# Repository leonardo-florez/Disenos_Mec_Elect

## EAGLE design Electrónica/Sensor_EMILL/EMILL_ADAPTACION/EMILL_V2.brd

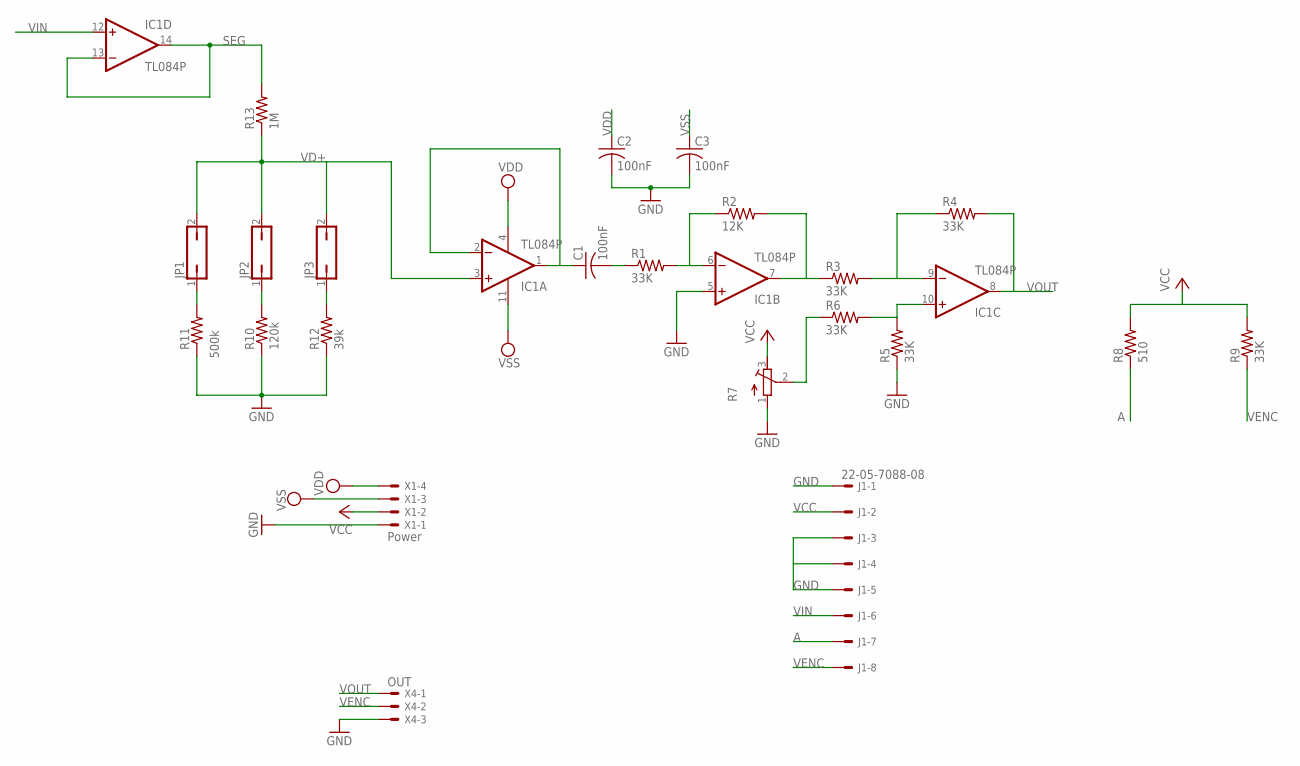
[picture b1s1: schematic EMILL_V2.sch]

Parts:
C1, C2, C3: 100nF; C025-025X050
IC1: TL084P; DIL14
J1: 22-05-7088-08; 7395-08
JP1, JP2, JP3: JP1Q; JP1
R1, R3, R4, R5, R6, R9: 33K; 0207/10
R2: 12K; 0207/10
R7: R-TRIMM64W; RTRIM64W
R8: 510; 0207/10
R10: 120k; 0207/10
R11: 500k; 0207/10
R12: 39k; 0207/10
R13: 1M; 0207/10
X1: Power; 22-23-2041
X4: OUT; 22-23-2031

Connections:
A: J1.7, R8.1
GND: C2.2, C3.2, IC1.5 (+IN), J1.1, J1.3, J1.4, J1.5, R5.1, R7.1 (A), R10.1, R11.1, R12.1, X1.1, X4.3
unnamed: C1.1, IC1.1 (OUT), IC1.2 (-IN)
unnamed: C1.2, R1.1
unnamed: IC1.6 (-IN), R1.2, R2.1
unnamed: IC1.7 (OUT), R2.2, R3.1
unnamed: IC1.9 (-IN), R3.2, R4.1
unnamed: IC1.10 (+IN), R5.2, R6.2
unnamed: R6.1, R7.2 (S)
unnamed: JP2.1, R10.2
unnamed: JP3.1, R12.2
unnamed: JP1.1, R11.2
SEG: IC1.13 (-IN), IC1.14 (OUT), R13.2
VCC: J1.2, R7.3 (E), R8.2, R9.2, X1.2
VD+: IC1.3 (+IN), JP1.2, JP2.2, JP3.2, R13.1
VDD: C2.1, IC1.4 (V+), X1.4
VENC: J1.8, R9.1, X4.2
VIN: IC1.12 (+IN), J1.6
VOUT: IC1.8 (OUT), R4.2, X4.1
VSS: C3.1, IC1.11 (V-), X1.3

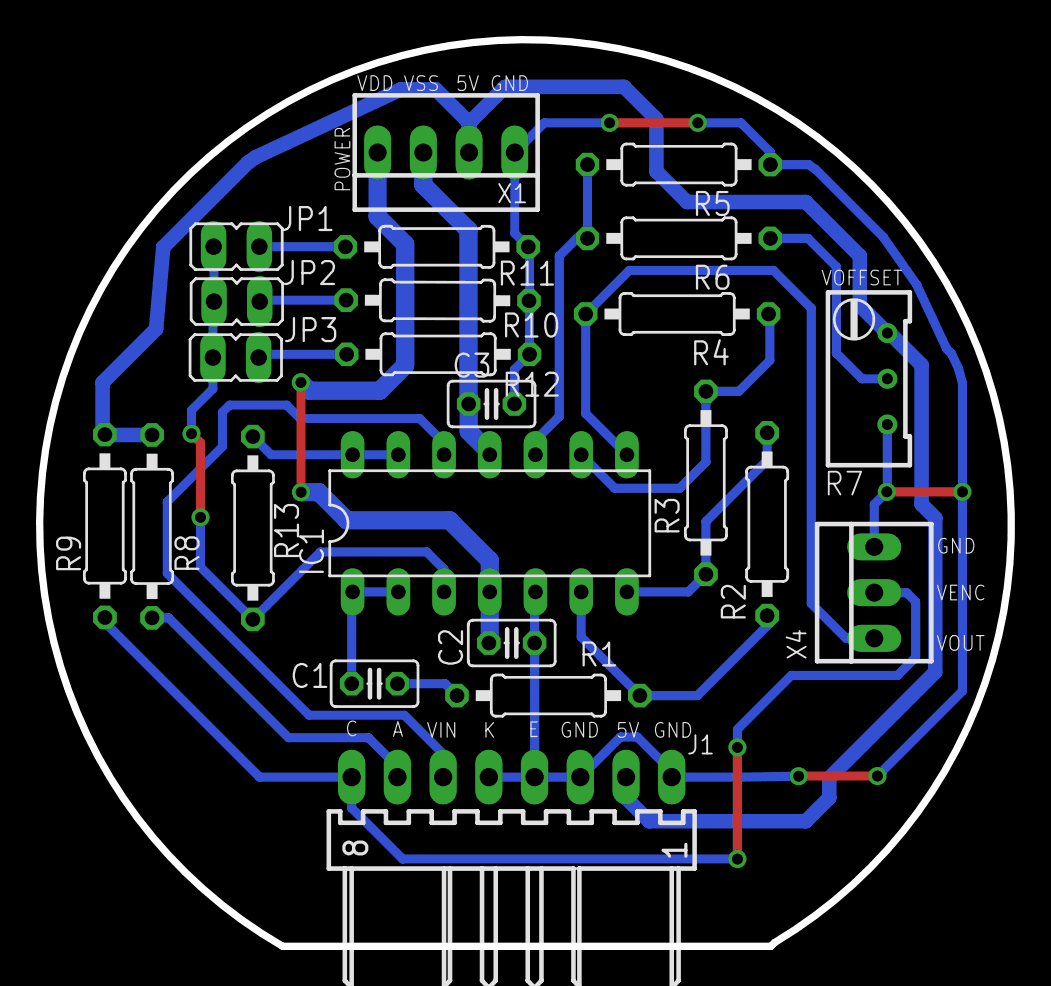
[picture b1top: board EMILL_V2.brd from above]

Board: 2 copper layers, 54.0 x 50.4 mm, 23 parts (0 on the bottom side), 20 nets.

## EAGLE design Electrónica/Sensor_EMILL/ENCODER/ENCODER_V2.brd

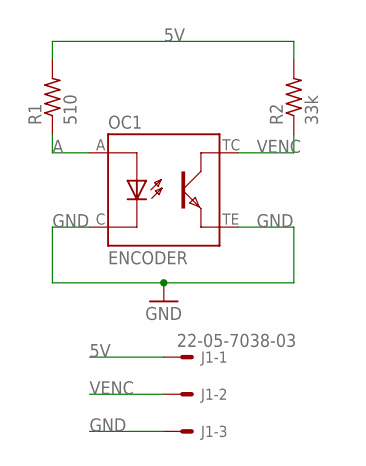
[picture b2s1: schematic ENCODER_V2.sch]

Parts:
J1: 22-05-7038-03; 7395-03
OC1: ENCODER; PI_GP1S53VJ000F
R1: 510; R0805
R2: 33k; R0805

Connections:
5V: J1.1, R1.2, R2.2
A: OC1.A, R1.1
GND: J1.3, OC1.C, OC1.TE
VENC: J1.2, OC1.TC, R2.1

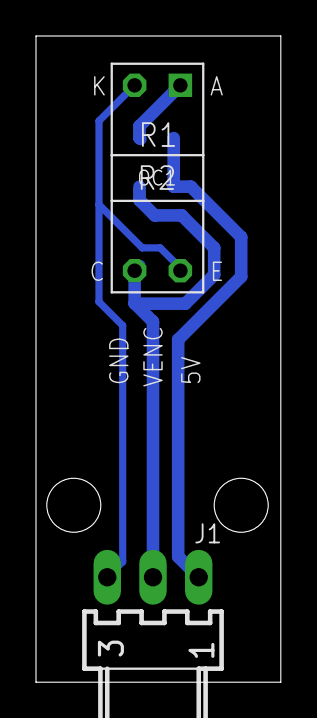
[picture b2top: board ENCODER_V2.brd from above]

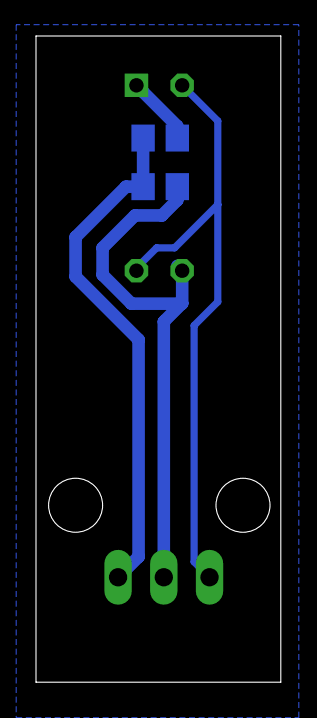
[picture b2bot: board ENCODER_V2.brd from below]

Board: 2 copper layers, 13.6 x 35.9 mm, 4 parts (2 on the bottom side), 4 nets.

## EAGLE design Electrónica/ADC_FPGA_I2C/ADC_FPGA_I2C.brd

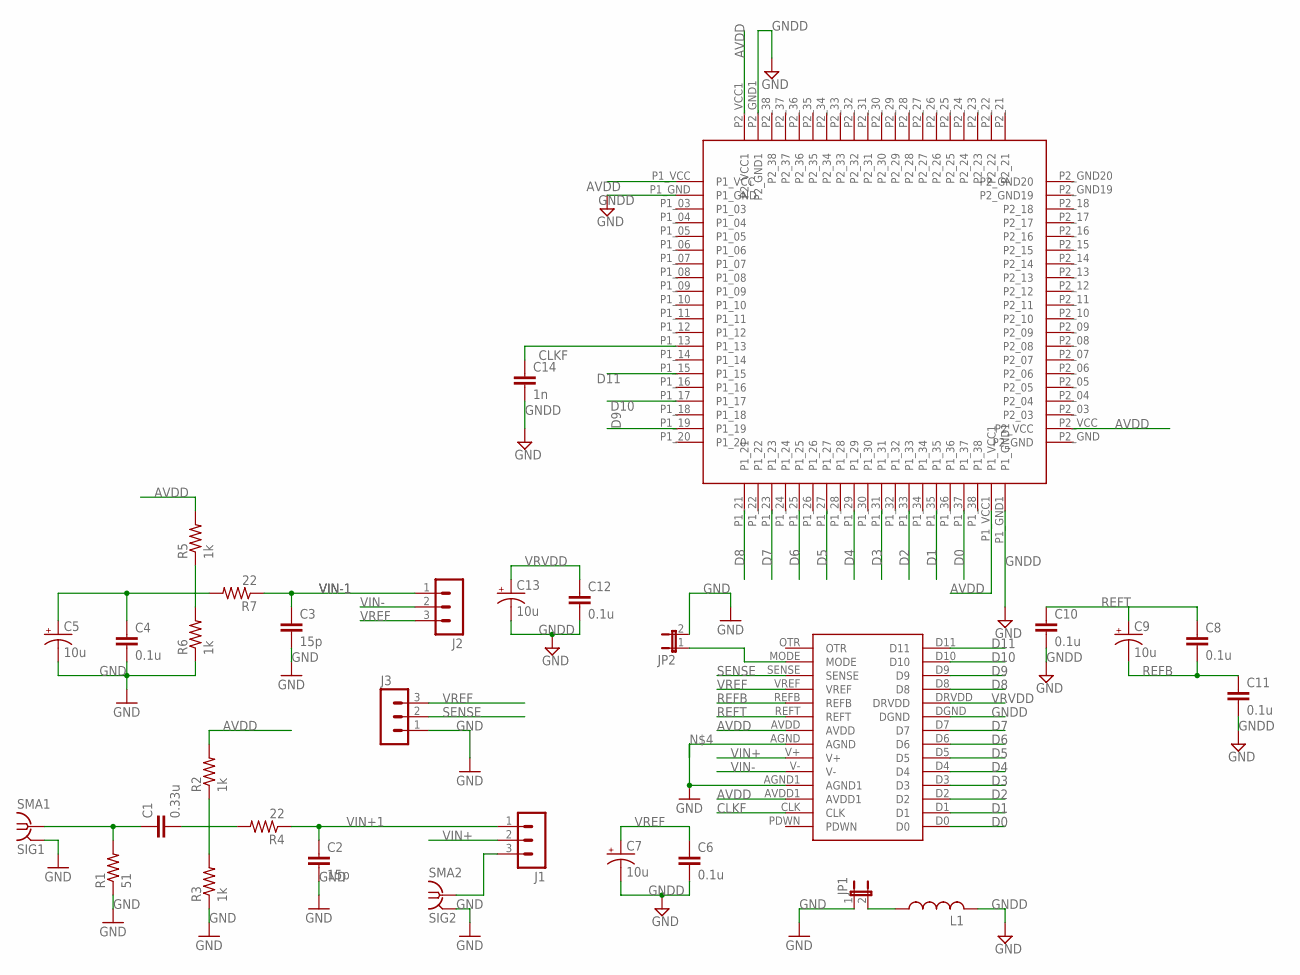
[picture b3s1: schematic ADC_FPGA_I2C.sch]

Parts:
C1: 0.33u; C075-063X106
C2, C3: 15p; C050-024X044
C4, C6, C8, C10, C11, C12: 0.1u; C050-024X044
C5, C7, C9, C13: 10u; E2,5-5
C14: 1n; C050-024X044
J1, J2, J3: MA03-1
JP1, JP2: JP1E; JP1
L1: L-US0204/7; 0204/7
R1: 51; 0207/10
R2, R3, R5, R6: 1k; 0207/10
R4, R7: 22; 0207/10
SMA1: SIG1; SMA-142-0701-871
SMA2: SIG2; SMA-142-0701-871
U$1: AD9235
U$2: SPARTAN_6_NIMAS

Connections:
AVDD: R2.2, R5.2, U$1.AVDD, U$1.AVDD1, U$2.P1_VCC, U$2.P1_VCC1, U$2.P2_VCC, U$2.P2_VCC1
CLKF: C14.1, U$1.CLK, U$2.P1_13
D0: U$1.D0, U$2.P1_37
D1: U$1.D1, U$2.P1_35
D2: U$1.D2, U$2.P1_33
D3: U$1.D3, U$2.P1_31
D4: U$1.D4, U$2.P1_29
D5: U$1.D5, U$2.P1_27
D6: U$1.D6, U$2.P1_25
D7: U$1.D7, U$2.P1_23
D8: U$1.D8, U$2.P1_21
D9: U$1.D9, U$2.P1_19
D10: U$1.D10, U$2.P1_17
D11: U$1.D11, U$2.P1_15
GND: C2.2, C3.2, C4.2, C5.-, J3.1, JP1.1, JP2.2, R1.1, R3.1, R6.1, SMA1.2@1 (2), SMA1.2@2 (2), SMA1.2@3 (2), SMA1.2@4 (2), SMA2.2@1 (2), SMA2.2@2 (2), SMA2.2@3 (2), SMA2.2@4 (2)
GNDD: C6.2, C7.-, C10.2, C11.2, C12.2, C13.-, C14.2, L1.2, U$1.DGND, U$2.P1_GND, U$2.P1_GND1, U$2.P2_GND1
unnamed: C1.1, R1.2, SMA1.1
unnamed: C1.2, R4.2
unnamed: R2.1, R3.2
unnamed: U$1.AGND, U$1.AGND1
unnamed: J1.3, SMA2.1
unnamed: C4.1, C5.+, R7.2
unnamed: R5.1, R6.2
unnamed: JP1.2, L1.1
unnamed: JP2.1, U$1.MODE
REFB: C8.2, C9.-, C11.1, U$1.REFB
REFT: C8.1, C9.+, C10.1, U$1.REFT
SENSE: J3.2, U$1.SENSE
VIN+: J1.2, U$1.V+
VIN+1: C2.1, J1.1, R4.1
VIN-: J2.2, U$1.V-
VIN-1: C3.1, J2.1, R7.1
VREF: C6.1, C7.+, J2.3, J3.3, U$1.VREF
VRVDD: C12.1, C13.+, U$1.DRVDD

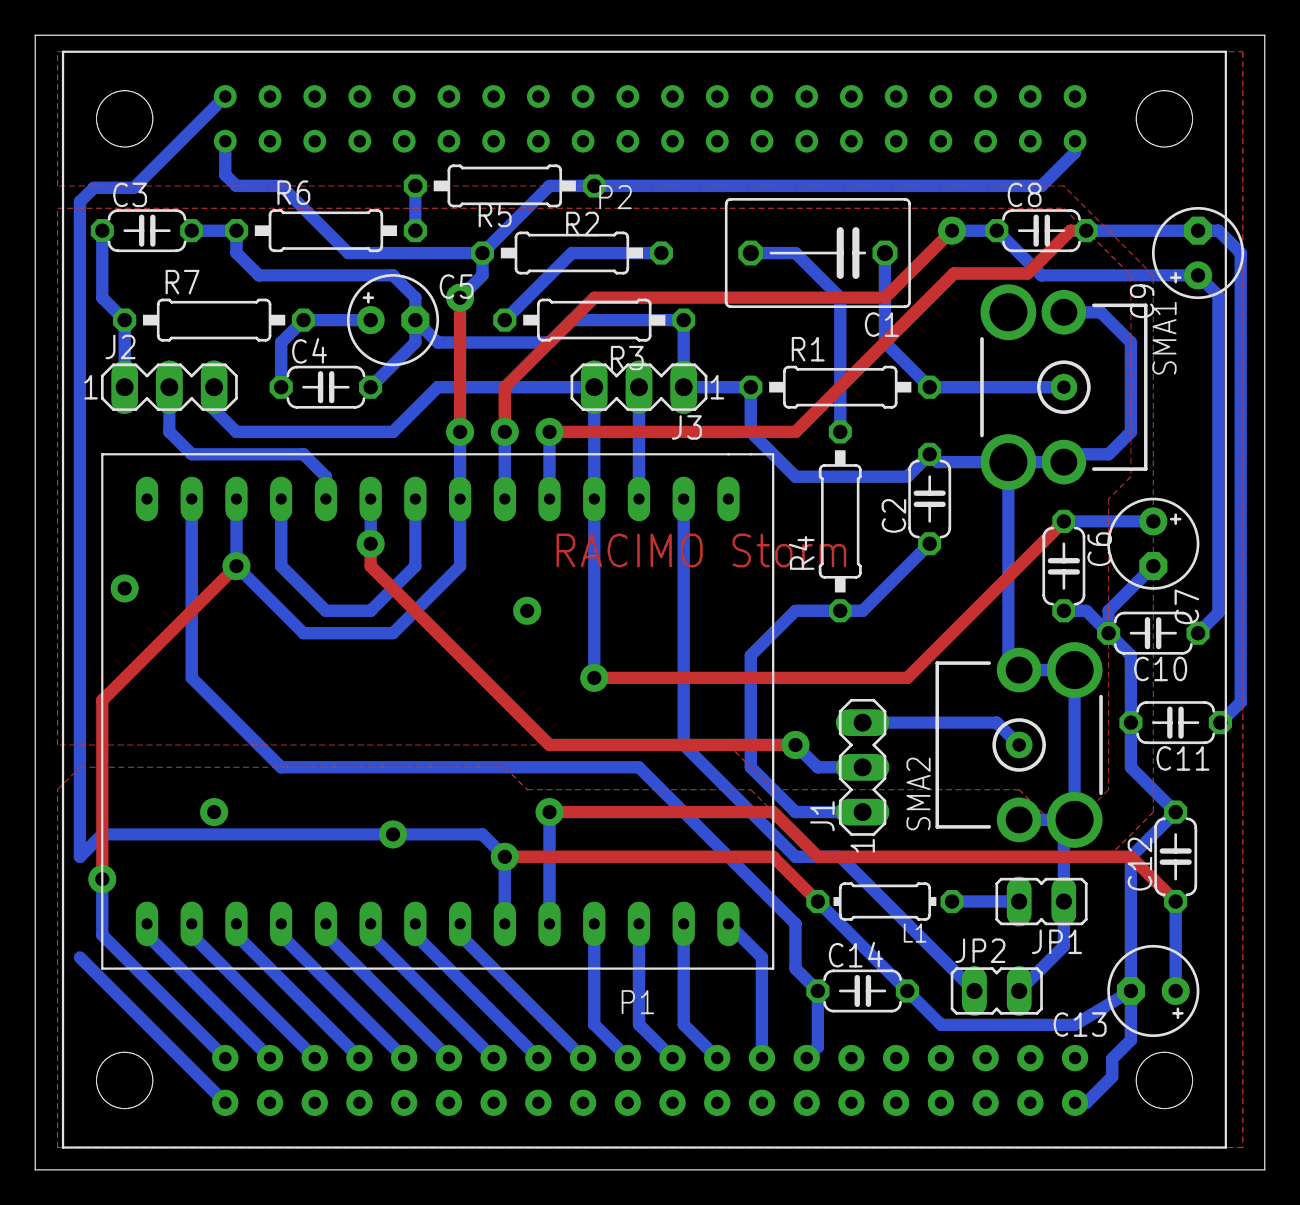
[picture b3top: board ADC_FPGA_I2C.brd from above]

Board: 2 copper layers, 69.8 x 64.4 mm, 31 parts (0 on the bottom side), 34 nets.

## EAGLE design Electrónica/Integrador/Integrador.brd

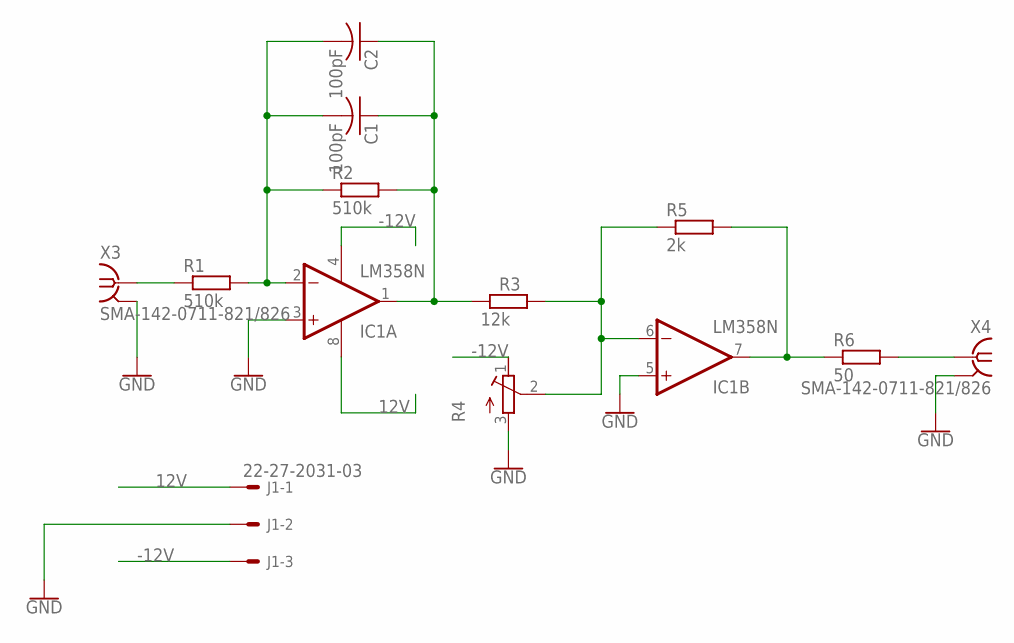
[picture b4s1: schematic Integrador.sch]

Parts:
C1, C2: 100pF; C025-030X050
IC1: LM358N; DIL08
J1: 22-27-2031-03; 6410-03
R1, R2: 510k; 0207/10
R3: 12k; 0207/10
R4: R-TRIMM3006P; RTRIM3006P
R5: 2k; 0207/10
R6: 50; 0207/10
X3, X4: SMA-142-0711-821/826; J502-ND-142-0711-821/826

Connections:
12V: IC1.8 (V+), J1.1
-12V: IC1.4 (V-), J1.3, R4.1 (E)
GND: IC1.3 (+IN), IC1.5 (+IN), J1.2, R4.3 (A), X3.G@1 (2), X3.G@2 (2), X3.G@3 (2), X3.G@4 (2), X4.G@1 (2), X4.G@2 (2), X4.G@3 (2), X4.G@4 (2)
unnamed: R1.1, X3.1
unnamed: C1.2, C2.2, IC1.2 (-IN), R1.2, R2.1
unnamed: C1.1, C2.1, IC1.1 (OUT), R2.2, R3.1
unnamed: IC1.6 (-IN), R3.2, R4.2 (S), R5.1
unnamed: IC1.7 (OUT), R5.2, R6.1
unnamed: R6.2, X4.1

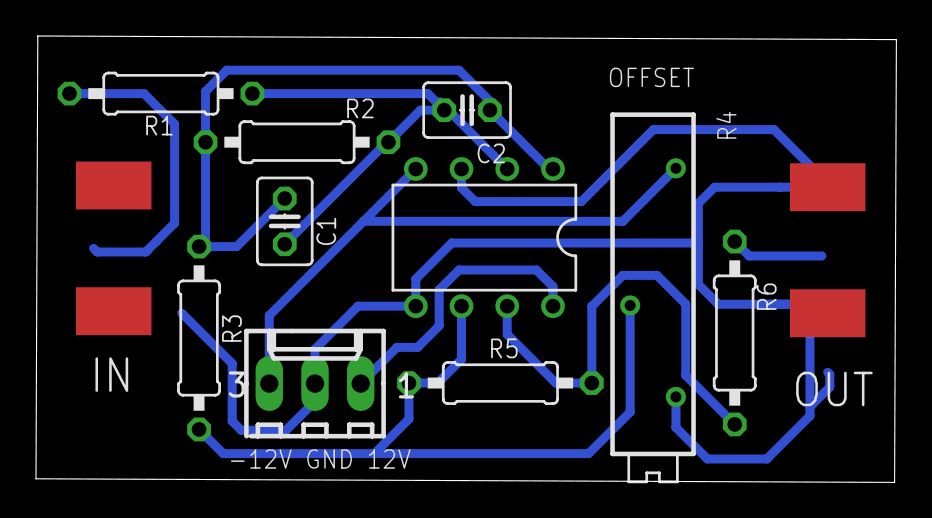
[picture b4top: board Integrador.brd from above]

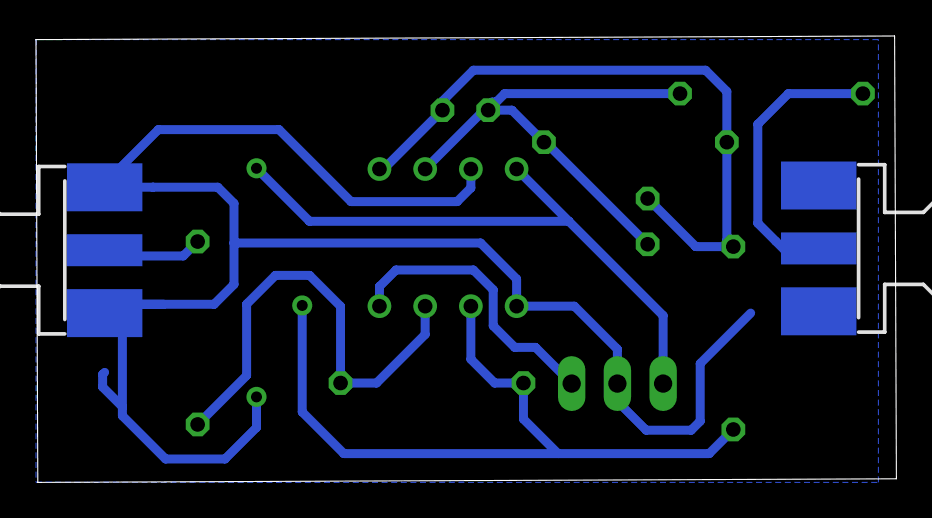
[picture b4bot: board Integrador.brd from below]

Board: 2 copper layers, 47.8 x 24.8 mm, 12 parts (2 on the bottom side), 9 nets.

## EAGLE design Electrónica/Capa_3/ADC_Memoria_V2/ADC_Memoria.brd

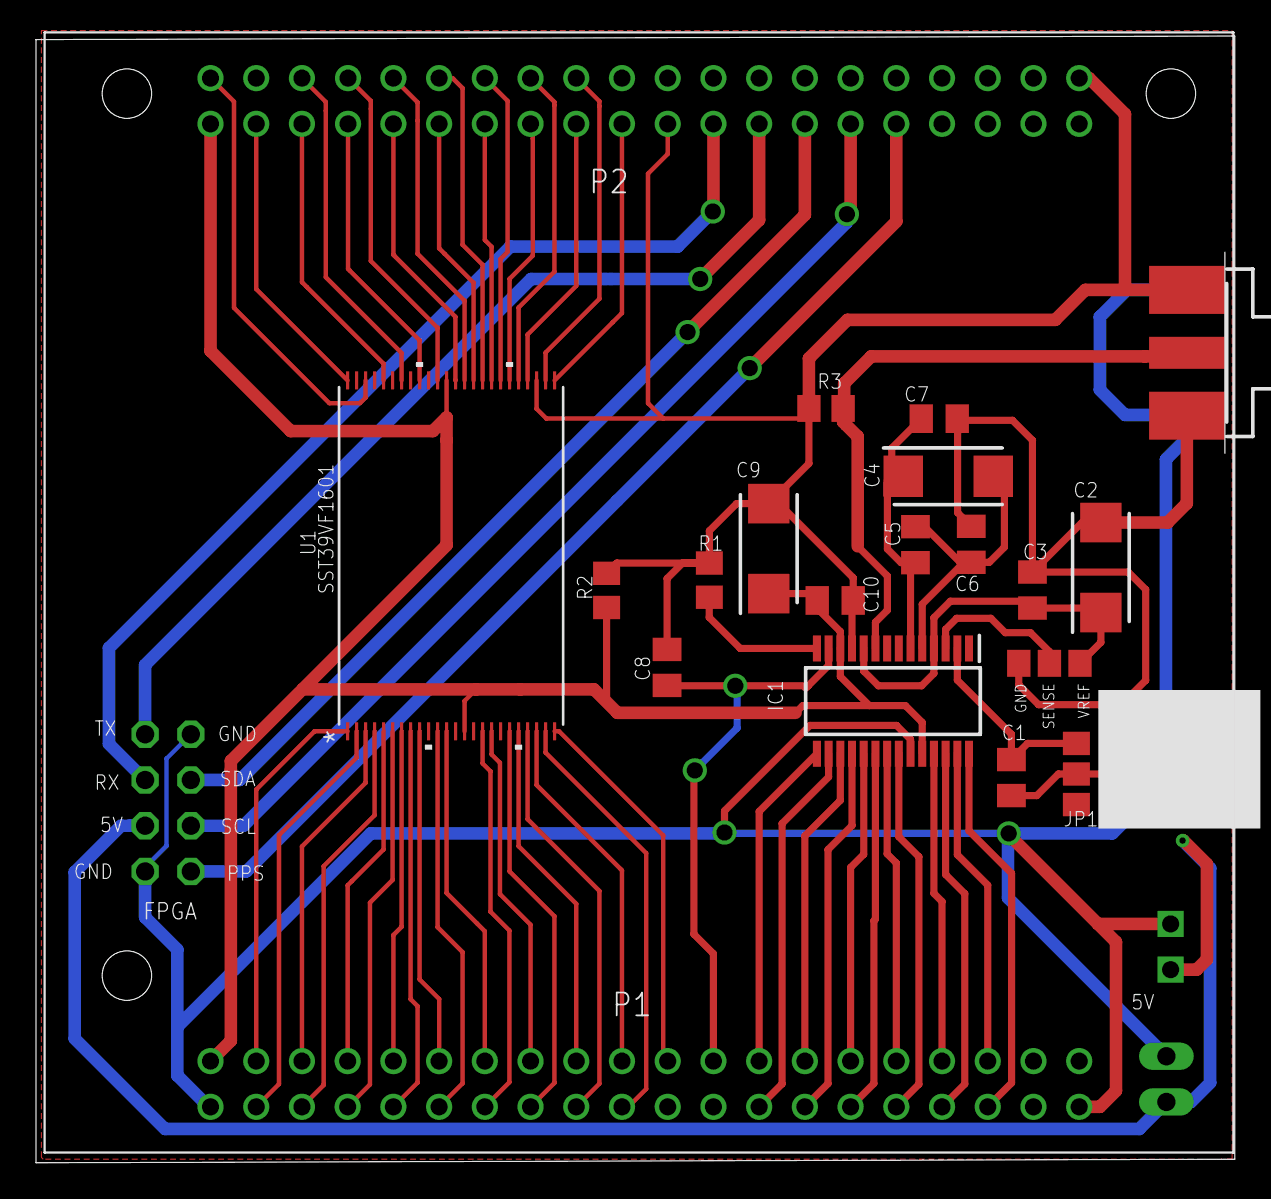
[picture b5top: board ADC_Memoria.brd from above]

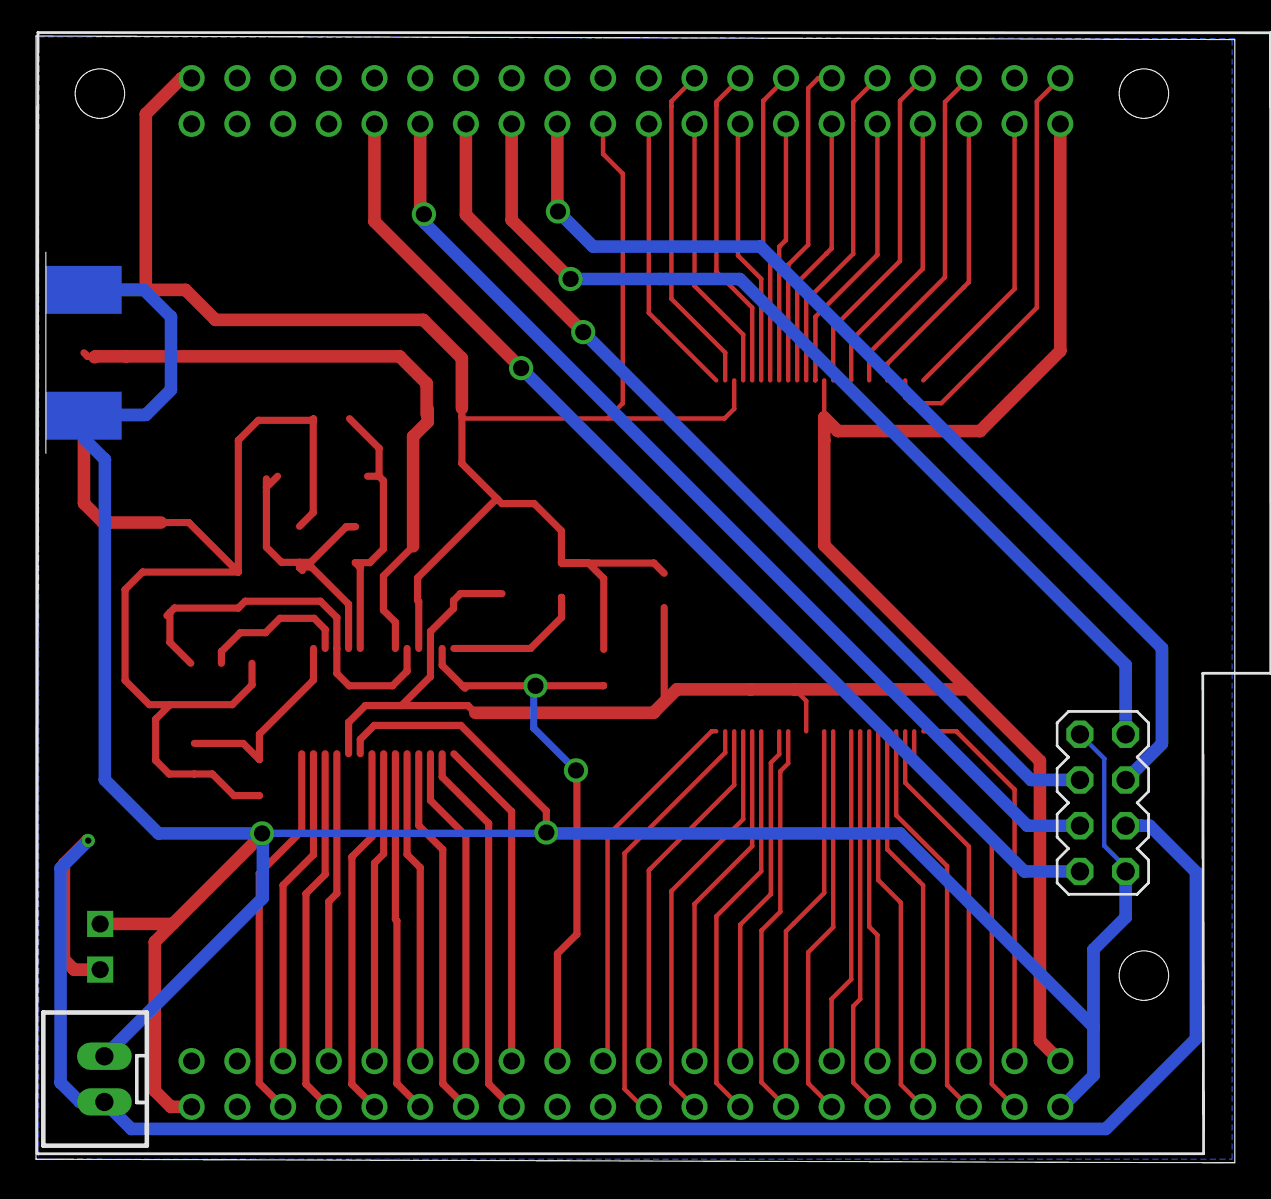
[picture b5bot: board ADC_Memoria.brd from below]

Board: 2 copper layers, 66.6 x 62.6 mm, 21 parts (2 on the bottom side), 63 nets.

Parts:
C1, C3, C5, C6, C7, C10: 0.1uF; C0805K
C2, C4, C9: 10uF; CAPPM6032X280N
C8: 15pF; C0805K
GND-SEN-VREF: JP2; A0R-JMP
IC1: AD9235; SOP65P638X110-28N
JP1: GND MODE; A0R-JMP
R1: 5k; R0805
R2: 10k; R0805
R3: 50; R0805
SMA: SIGNAL; J502-ND-142-0711-821/826
U1: SST39VF1601; TSOP48_EKE_SST-L
U$1: SPARTAN_NO_HOLES
U$2: CAPA1
V_EXT: V_Ext; JST-XH-02-PACKAGE-LONG-PAD

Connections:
5V: U$1.5V_E, U$2.5V, V_EXT.1
A0: U1.25, U$1.P2_22
A1: U1.24, U$1.P1_19
A2: U1.23, U$1.P1_22
A3: U1.22, U$1.P1_21
A4: U1.21, U$1.P1_24
A5: U1.20, U$1.P1_23
A6: U1.19, U$1.P1_26
A8: U1.8, U$1.P1_32
A9: U1.7, U$1.P1_31
A10: U1.6, U$1.P1_34
A11: U1.5, U$1.P1_33
A12: U1.4, U$1.P1_36
A13: U1.3, U$1.P1_35
A14: U1.2, U$1.P1_38
A15: U1.1, U$1.P1_37
A16: U1.48, U$1.P2_38
A17: U1.17, U$1.P1_25
A18: U1.16, U$1.P1_28
A19: U1.9, U$1.P1_29
AVDD: C9.1, C10.1, IC1.12, IC1.24, R2.1, U1.14, U1.37, U$1.P1_VCC1, U$1.P2_VCC1
CE: U1.26, U$1.P2_23
CLK: C8.1, IC1.13, U$1.P1_17
D0: IC1.15, U$1.P1_15
D1: IC1.16, U$1.P1_16
D2: IC1.17, U$1.P1_13
D3: IC1.18, U$1.P1_14
D4: IC1.19, U$1.P1_11
D5: IC1.20, U$1.P1_12
D6: IC1.21, U$1.P1_09
D7: IC1.22, U$1.P1_10
D8: IC1.25, U$1.P1_07
D9: IC1.26, U$1.P1_08
D10: IC1.27, U$1.P1_05
D11: IC1.28, U$1.P1_06
DQ0: U1.29, U$1.P2_25
DQ1: U1.31, U$1.P2_27
DQ2: U1.33, U$1.P2_29
DQ3: U1.35, U$1.P2_31
DQ4: U1.38, U$1.P2_33
DQ5: U1.40, U$1.P2_34
DQ6: U1.42, U$1.P2_35
DQ7: U1.44, U$1.P2_36
DQ8: U1.30, U$1.P2_26
DQ9: U1.32, U$1.P2_28
DQ10: U1.34, U$1.P2_30
DQ11: U1.36, U$1.P2_32
GND: C1.2, C2.2, C3.2, C6.2, C7.2, C8.2, C9.2, C10.2, GND-SEN-VREF.1, IC1.11, IC1.23, JP1.2, R1.1, R2.2, R3.1, SMA.G@1, SMA.G@2, SMA.G@3, SMA.G@4, U1.27, U1.46, U$1.GND_E, U$1.P1_GND, U$1.P1_GND1, U$1.P2_GND, U$1.P2_GND1, U$1.P2_GND20, U$2.GND, U$2.GND2, V_EXT.2
MODE: C1.1, IC1.2, JP1.1
unnamed: IC1.14, R1.2
OE: U1.28, U$1.P2_24
PPS: U$1.P2_10, U$2.PPS
REFB: C4.2, C5.2, C6.1, IC1.5
REFT: C4.1, C5.1, C7.1, IC1.6
RST: U1.12, U$1.P1_27
RX: U$1.P2_18, U$2.RX2PI
SCL: U$1.P2_12, U$2.SCL
SDA: U$1.P2_14, U$2.SDA
SENSE: GND-SEN-VREF.2, IC1.3
TX: U$1.P2_16, U$2.TX2PI
VIN: IC1.9, R3.2, SMA.1
VREF: C2.1, C3.1, GND-SEN-VREF.3, IC1.4, IC1.10
WE: U1.11, U$1.P1_30

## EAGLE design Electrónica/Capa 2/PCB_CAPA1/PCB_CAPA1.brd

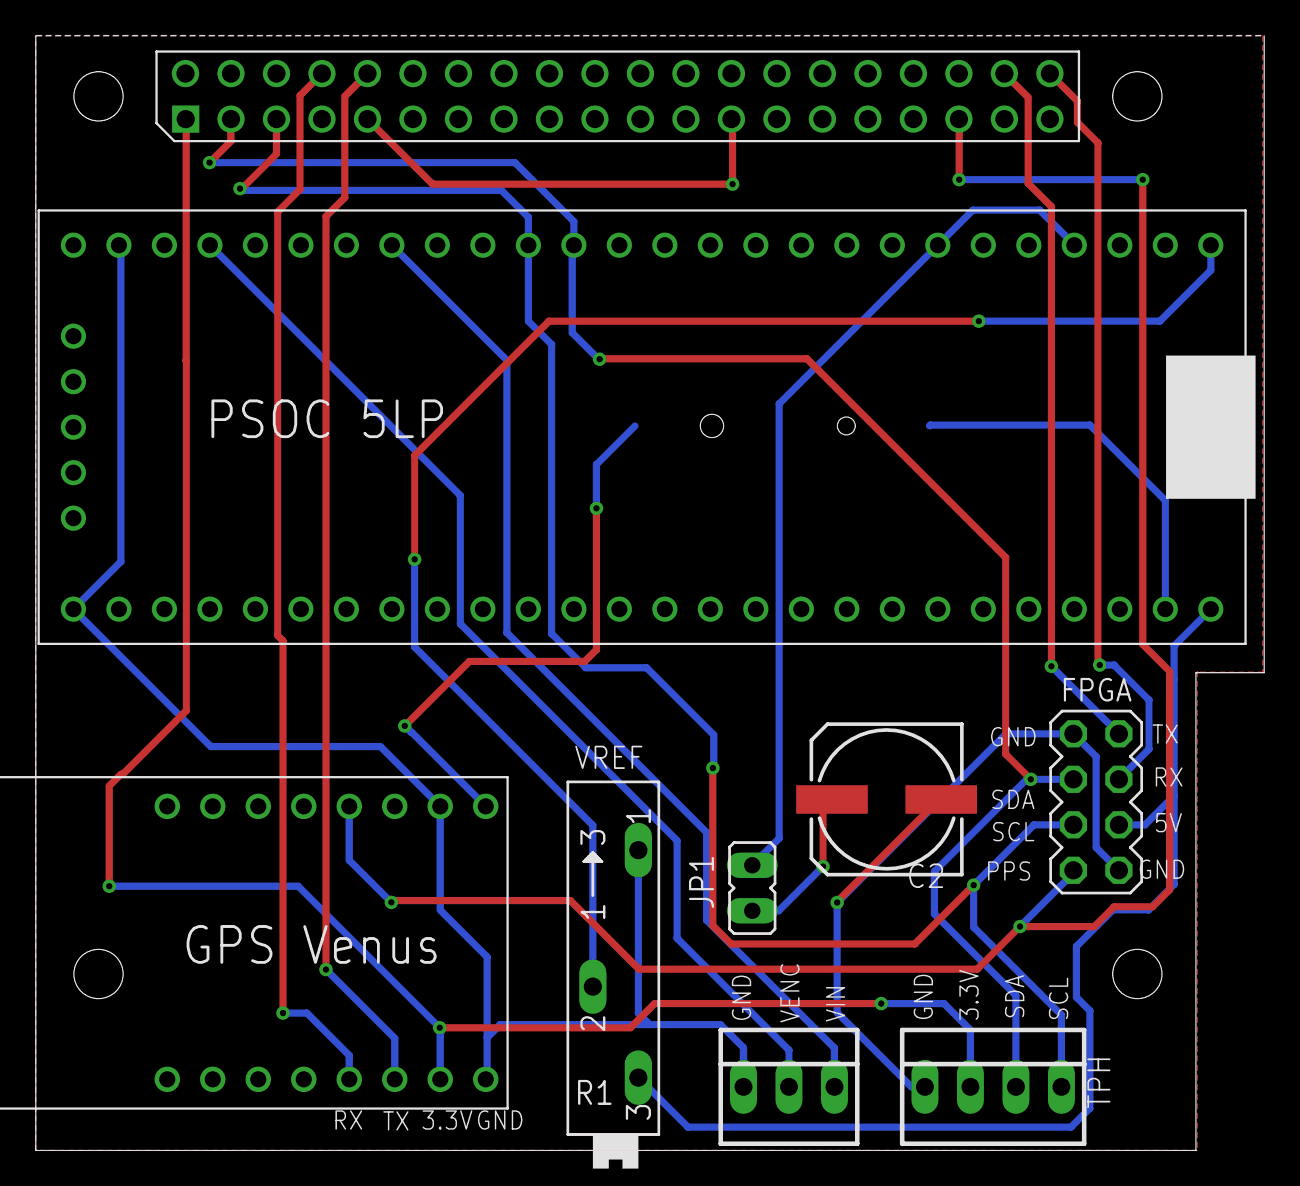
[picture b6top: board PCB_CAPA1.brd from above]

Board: 2 copper layers, 68.6 x 62.2 mm, 10 parts (1 on the bottom side), 16 nets.

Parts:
BAT1: 3V; CH291-1220LF
C2: 153CLV-0807
FPGA: MA04-2
GPS: GPS_VENUS
JP1: JP1
PCB1: RPI3RPI3; RPI3
R1: SP19L
U$1: PSOC_5LP
X1: SENSOR TPH; 22-23-2041
X2: EMILL; 22-23-2031

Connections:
3.3V: GPS.3.3V, PCB1.P$1, X1.2
5V: FPGA.3, R1.E, U$1.VDD
GND: BAT1.-, C2.-, FPGA.1, FPGA.8, GPS.GND, GPS.GND1, PCB1.P$9, PCB1.P$25, PCB1.P$39, R1.A, U$1.GND, U$1.GND2, U$1.GND3, X1.1, X2.1
unnamed: BAT1.+, GPS.VBAT
unnamed: C2.+, JP1.1
PPS: FPGA.2, GPS.PPS, PCB1.P$35
RX2PI: FPGA.5, PCB1.P$40
RXPI: GPS.TX0, PCB1.P$10
SCL: FPGA.4, PCB1.P$5, U$1.SCL, X1.4
SDA: FPGA.6, PCB1.P$3, U$1.SDA, X1.3
TX2PI: FPGA.7, PCB1.P$38
TXPI: GPS.RX0, PCB1.P$8
VDC: JP1.2, U$1.2.3, U$1.2.6
VENC: U$1.1.6, X2.2
VIN: U$1.1.2, X2.3
VREF: R1.S, U$1.2.0

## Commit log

2020-03-02 Diseños de PCB usados hasta la fecha. 1 Marzo. Lo diseños estan hechos en Eagle
2020-03-04 Versión 3 de la PCB que integra la memoria con el ADC
2020-03-05 Actualiización de resistencia empaquetado 1206, Proteccion de tensión, Perforaciones de 3 mm, áreas blancas de la huella de la FPGA
2020-03-05 Aumento de ancho de banda usando el OPA4228
2020-03-07 Integrador con 5.2 cm de largo y usando el opa4228
2020-04-25 Nueva organizacion
2020-04-25 cambios
    dfad
2020-04-25 Revert "cambios"
    This reverts commit 61f00a9271ceec6bd11cc11396300cb521a5136d.
2020-04-25 Capa dos estación de monitoreo
    Contiene los archivos sch y brd
2020-04-25 PCB de adaptación emill
2020-04-25 Encoder sensor emill
2020-04-25 Adicionar Capa 2 y PCB de adaptacion
2020-04-25 Cambio nombre

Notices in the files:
parts and their libraries:
SparkFun-PowerSymbols: Licensing: Creative Commons ShareAlike 4.0 International - https://creativecommons.org/licenses/by-sa/4.0
